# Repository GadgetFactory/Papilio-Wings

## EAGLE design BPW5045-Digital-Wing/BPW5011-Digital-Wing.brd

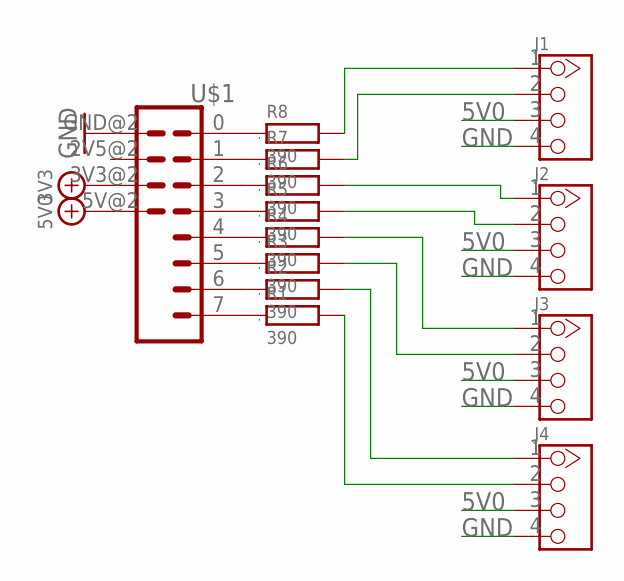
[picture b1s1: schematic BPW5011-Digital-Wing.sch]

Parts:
J1, J2, J3, J4: CONNECTOR_TWIG-2.0-LEADED; CONNECTOR_4P-LEADED-2.0
R1, R2, R3, R4, R5, R6, R7, R8: 390; 0805
U$1: WING8WING8_NOHOLES; WINGSIDE_8BIT_NOHOLES

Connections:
3V3: U$1.3V3@2 (3V3)
5V0: J1.3, J2.3, J3.3, J4.3, U$1.5V@2 (5V)
GND: J1.4, J2.4, J3.4, J4.4, U$1.GND@2 (GND)
unnamed: J1.1, R8.2
unnamed: J1.2, R7.2
unnamed: J2.1, R6.2
unnamed: J2.2, R5.2
unnamed: J3.1, R4.2
unnamed: J3.2, R3.2
unnamed: J4.1, R2.2
unnamed: J4.2, R1.2
unnamed: R1.1, U$1.7 (8)
unnamed: R2.1, U$1.6 (7)
unnamed: R3.1, U$1.5 (6)
unnamed: R4.1, U$1.4 (5)
unnamed: R5.1, U$1.3 (4)
unnamed: R6.1, U$1.2 (3)
unnamed: R7.1, U$1.1 (2)
unnamed: R8.1, U$1.0 (1)

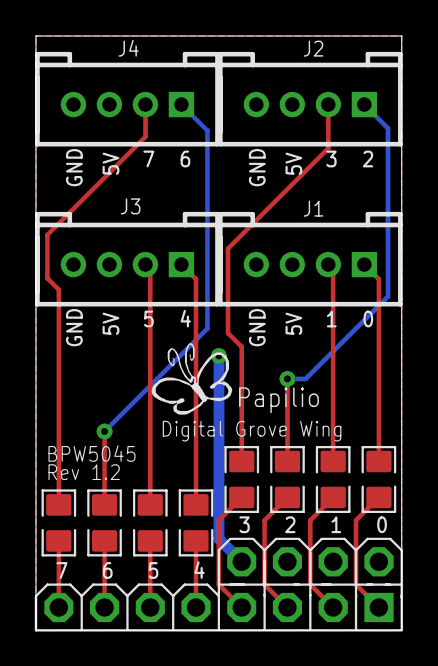
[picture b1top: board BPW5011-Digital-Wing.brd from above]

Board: 2 copper layers, 20.3 x 33.0 mm, 14 parts (0 on the bottom side), 18 nets.

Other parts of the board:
U$2: GADGETFACTORY_LOGO
